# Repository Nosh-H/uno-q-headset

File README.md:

# The Headset - Uno Q Version

The Headset (Uno Q Version) is a prototype control system for a wearable headset built around an Arduino Uno Q and a Python web app. The goal is to coordinate physical hardware behavior on the microcontroller with remote control from a browser over the local network, in order to automate the application of a cold compress on the wearer's eyes for the goal of treating eye itching and pain caused by allergies.

This repository currently contains two main parts:

- A Python FastAPI app that exposes the web UI and API
- An Arduino/C++ sketch that owns the hardware-side behavior and RPC handlers

## What The Project Does

- Serves a lightweight web UI for controlling the headset
- Sends commands from the browser to Python
- Forwards those commands from Python to the microcontroller through the Arduino bridge
- Polls hardware state in the background so the UI can display live status
- Handles immediate hardware behavior on the MCU, where timing and safety matter most

## Architecture

The active control path is:

`browser -> python/main.py -> python/controller.py -> python/bridge_client.py -> sketch/sketch.ino`

More specifically:

- `python/main.py` defines the FastAPI app and the HTTP routes
- `python/controller.py` owns runtime state and background polling
- `python/bridge_client.py` wraps bridge calls to the microcontroller
- `sketch/sketch.ino` registers RPC functions with `Bridge.provide(...)`
- `python/arduino/` contains the vendored Arduino bridge support library

## Repository Layout

- `python/` - Python application code, API routes, controller logic, and bridge wrapper
- `sketch/` - Arduino Uno Q firmware and hardware logic
- `assets/` - Project assets
- `.agents/` - Assistant instructions and related guidance
- `README.md` - This overview

## Current UI And API

The current Python app serves an inline HTML page from `python/main.py`. It exposes API endpoints for:

- `GET /api/status`
- `GET /api/state/{side}`
- `POST /api/state/{side}`
- `GET /api/temp/{side}`
- `POST /api/led`
- `POST /api/mode`
- `POST /api/stop`

The page polls status periodically and sends commands back to the controller. The controller also mirrors the arm state and temperatures returned by the firmware bridge so the browser can read them back without talking to the MCU directly.

## Hardware Control In The Sketch

The C++ side is structured as a small embedded control loop rather than a collection of one-off callbacks. In `sketch/sketch.ino`, the firmware keeps the live hardware state in a few shared variables (arm state, LED state, current mode) and updates them through RPC handlers registered with the Bridge. Those handlers are intentionally lightweight: they change control state or request a mode transition, while the `periodic()` loop is responsible for quickly applying that state to the hardware.

The supporting C++ files reinforce that split: 
- Pin mapping and board-specific constants live in `sketch/Constants.hpp`
- Button handling is wrapped in `DigitalInput` for debouncing and edge detection
- Temperature sensing is isolated in `Thermometer` so the main sketch can treat sensing as a service rather than embedding hardware details inline. 

This way, the firmware can keep safety-sensitive behavior local to the microcontroller and avoid relying on web requests for timing.

Motor control is still in progress, but the architecture already has the intended structure: main.cpp computes desired setpoints from the current arm state, and the lower-level DCMotor.hpp consumes those setpoints once it is fully wired up.

## Working On The Codebase

- Keep changes small and readable.
- Update the firmware RPC, `BridgeClient`, controller, route handler, and UI together when adding a new command.
- Treat `python/arduino/` as vendored framework code unless you are intentionally fixing the shared bridge library.
- Keep hardware timing and safety-sensitive behavior in the firmware, not in the web server.
- Validate inputs at the API boundary.
- Preserve thread safety in `ProjectController`, which owns the live state and polling loop.

## Notes

- This is still a prototype, so some bridge calls and hardware behaviors may be placeholders or incomplete.
- If a Python command does not line up with a firmware RPC, update both sides together instead of assuming one side is correct.
- The root README is intentionally focused on orientation. The deeper implementation details belong in code comments and the assistant instructions.

## License
This program is free software: you can redistribute it and/or modify it under the terms of the GNU General Public License as published by the Free Software Foundation, either version 3 of the License, or any later version.

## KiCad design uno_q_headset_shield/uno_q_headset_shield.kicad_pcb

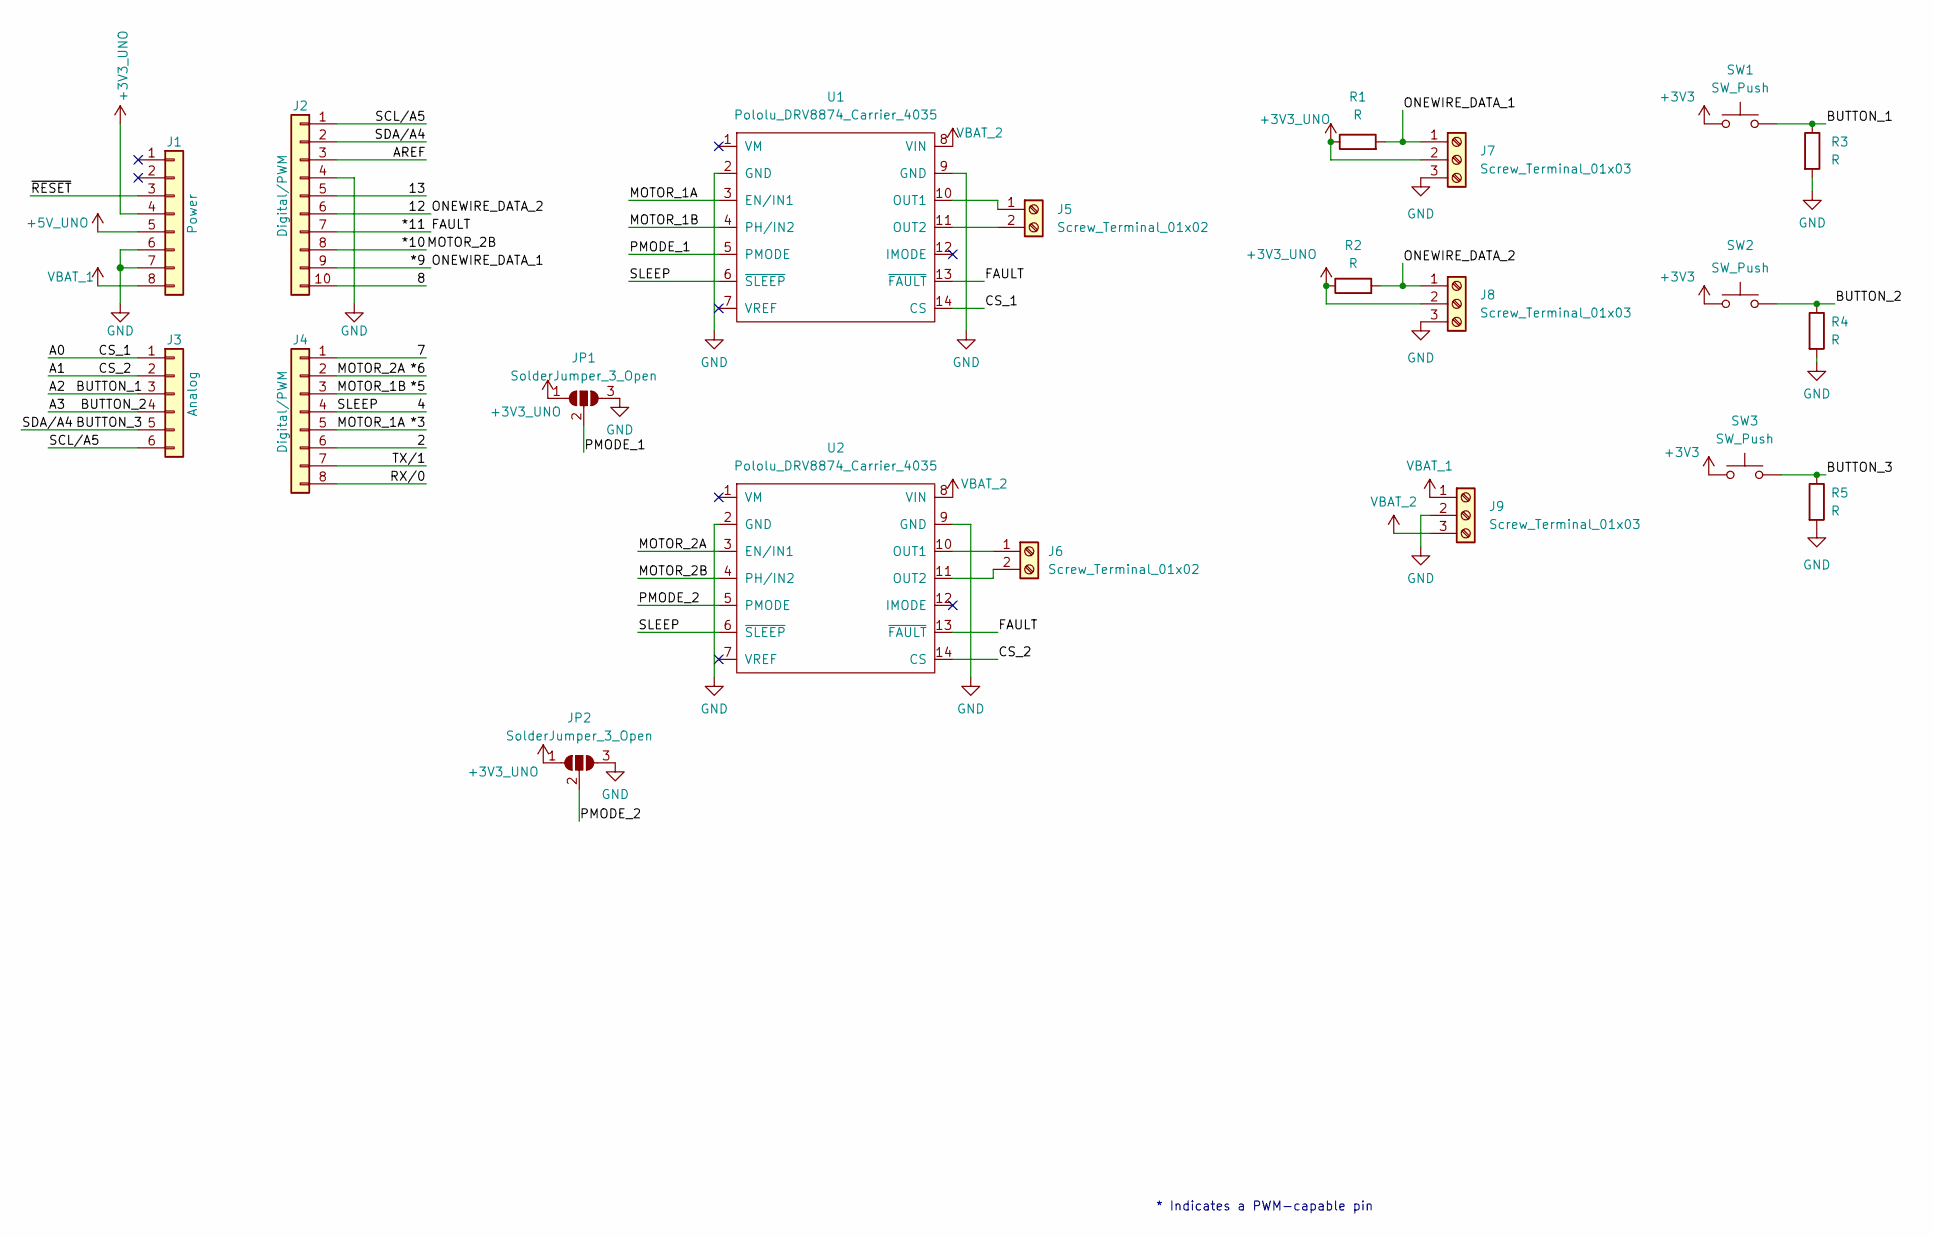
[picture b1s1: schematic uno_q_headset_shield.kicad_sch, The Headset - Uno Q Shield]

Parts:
J1: Power; PinSocket_1x08_P2.54mm_Vertical
J2: Digital/PWM; PinSocket_1x10_P2.54mm_Vertical
J3: Analog; PinSocket_1x06_P2.54mm_Vertical
J4: Digital/PWM; PinSocket_1x08_P2.54mm_Vertical
J5, J6: Screw_Terminal_01x02; TerminalBlock_Phoenix_MKDS-1,5-2-5.08_1x02_P5.08mm_Horizont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
J7, J8, J9: Screw_Terminal_01x03; TerminalBlock_Phoenix_MKDS-1,5-3-5.08_1x03_P5.08mm_Horizont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
JP1, JP2: SolderJumper_3_Open; SolderJumper-3_P2.0mm_Open_TrianglePad1.0x1.5mm_NumberLabels
R1, R2, R3, R4, R5: R; R_1206_3216Metric_Pad1.30x1.75mm_HandSolder
SW1, SW2, SW3: SW_Push; SW_Push_1P1T_NO_CK_KSC6xxJ
U1, U2: Pololu_DRV8874_Carrier_4035; DRV887X_Carrier

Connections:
+3V3: SW1.1, SW2.1, SW3.1
+3V3_UNO: J1.4, J7.2, J8.2, JP1.1 (A), JP2.1 (A), R1.1, R2.1
+5V_UNO: J1.5
/2: J4.6
/4: J4.4, U1.6 (~SLEEP), U2.6 (~SLEEP)
/7: J4.1
/8: J2.10
/12: J2.6, J8.1, R2.2
/13: J2.5
/*3: J4.5, U1.3 (EN/IN1)
/*5: J4.3, U1.4 (PH/IN2)
/*6: J4.2, U2.3 (EN/IN1)
/*9: J2.9, J7.1, R1.2
/*10: J2.8, U2.4 (PH/IN2)
/*11: J2.7, U1.13 (~FAULT), U2.13 (~FAULT)
/A0: J3.1, U1.14 (CS)
/A1: J3.2, U2.14 (CS)
/A2: J3.3, R3.1, SW1.2
/A3: J3.4, R4.1, SW2.2
/AREF: J2.3
/BUTTON_3: J2.2, J3.5, R5.1, SW3.2
/PMODE_1: JP1.2 (C), U1.5 (PMODE)
/PMODE_2: JP2.2 (C), U2.5 (PMODE)
/RX/0: J4.8
/SCL/A5: J2.1, J3.6
/TX/1: J4.7
/~RESET: J1.3
GND: J1.6, J1.7, J2.4, J7.3, J8.3, J9.2, JP1.3 (B), JP2.3 (B), R3.2, R4.2, R5.2, U1.2 (GND), U1.9 (GND), U2.2 (GND), U2.9 (GND)
unnamed: J5.1, U1.10 (OUT1)
unnamed: J5.2, U1.11 (OUT2)
unnamed: J6.1, U2.10 (OUT1)
unnamed: J6.2, U2.11 (OUT2)
VBAT_1: J1.8, J9.1
VBAT_2: J9.3, U1.8 (VIN), U2.8 (VIN)

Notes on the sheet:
* Indicates a PWM-capable pin

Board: 2 copper layers, 25 parts (0 on the bottom side), 25 nets, no tracks yet.

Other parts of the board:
MH1, MH2, MH3, MH4: MountingHole_3.2mm
